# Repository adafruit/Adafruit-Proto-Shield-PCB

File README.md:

## Adafruit Proto Shield for Arduino Unassembled Kit - Stackable - Version R3 PCB

<a href="http://www.adafruit.com/products/2077"><br/>
Click here to purchase one from the Adafruit shop</a>

PCB files for the Adafruit Proto Shield for Arduino Unassembled Kit - Stackable - Version R3. Format is EagleCAD schematic and board layout
* https://www.adafruit.com/product/2077

### Description

This prototyping shield is the best out there (well, we think so, at least), and now is even better with **Version R3** - updated for the most compatibility with just about all the Arduinos! It works with UNO, Mega, Leonardo, NG, Diecimila, Duemilanove, and compatible Arduinos. Yun's and Arduino Ethernets have a chunky Ethernet jack that gets in the way of stacking, you can use the stacking headers included and it will work, just doesn't sit nice and flat.

Check out these awesome specifications:

 * It has a nice standard 0.1"x0.1" prototying grid with big pads
 * Comes with Stacking headers and plain header, choose whichever you want when soldering together
 * A IC pattern for adding DIP ICs up to 20 pins
 * Power rails down the middle and sides
 * A reset button and an extra general use button
 * 2 3mm general use LEDs, red and green, as well as 2 matching resistors
 * A pass-thru ICSP stacking header so you can stack any kind of shield on top, and/or use an AVR programmer
 * A surface-mount chip area for up to 14 SOIC size parts
 * Compatible with tiny breadboards
 * Every pin is brought out!
 * Gold plated pads
 * 2 x 0.1uF capacitors on either side for extra power stability
**Comes as a kit of parts** so you can choose how you want to configure your shield. However its very easy to assemble even for beginning solderers. [More information & instructions are available here](http://learn.adafruit.com/adafruit-proto-shield-arduino).

**Arduino and breadboards are not included!**

### License

Adafruit invests time and resources providing this open source design, please support Adafruit and open-source hardware by purchasing products from [Adafruit](https://www.adafruit.com)!

Designed by Limor Fried/Ladyada for Adafruit Industries.

Creative Commons Attribution/Share-Alike, all text above must be included in any redistribution. See license.txt for additional details.

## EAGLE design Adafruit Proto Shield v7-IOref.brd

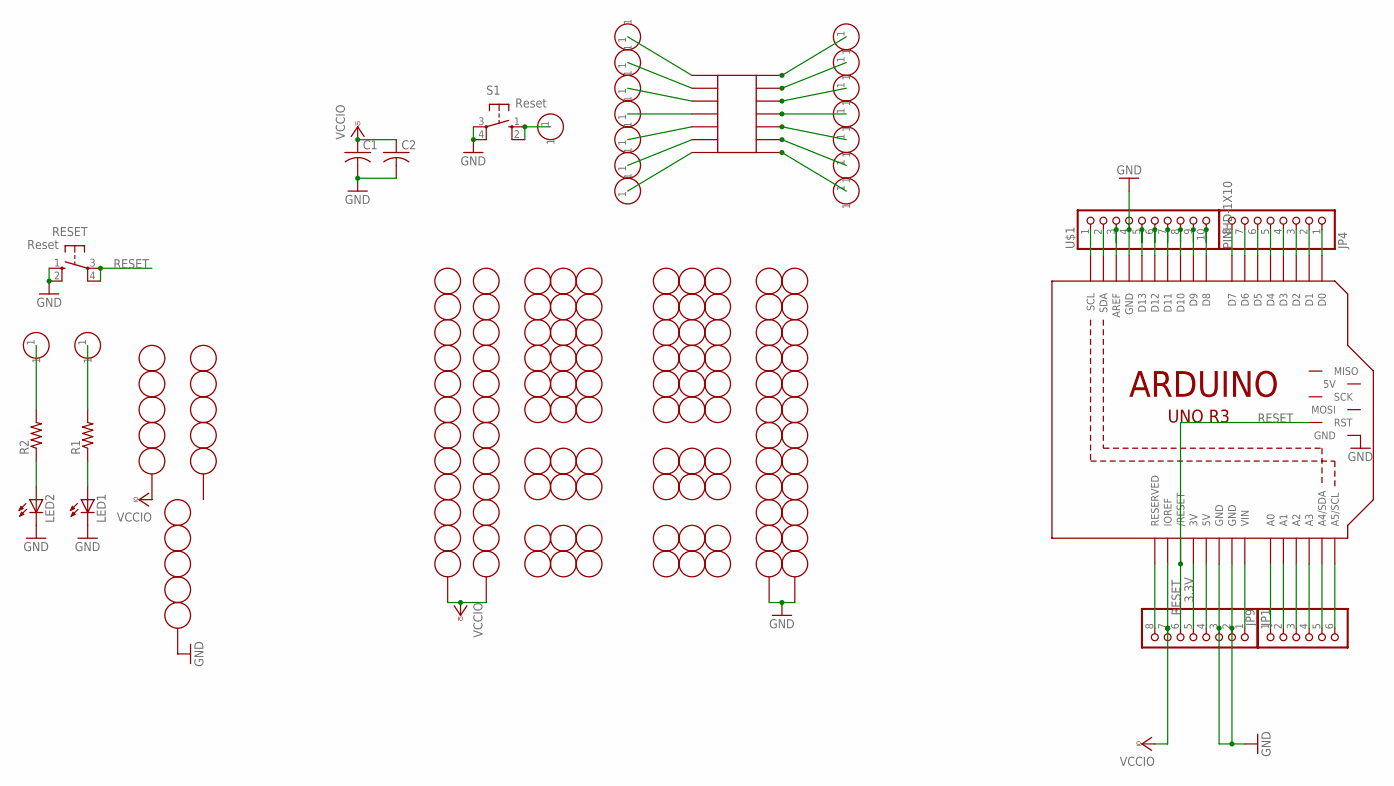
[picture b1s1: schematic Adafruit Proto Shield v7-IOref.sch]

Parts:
C1, C2: C-US025-025X050; C025-025X050
GNDSTRIP1, GNDSTRIP2: 12-STRIP
IC1: SMD-14; SO-14NMW
JP1, JP4: PINHD-1X8BIG; 1X08-BIG
JP9: PINHD-1X6B; 1X06-BIG
LED1, LED2: LED3MM
M1: ARDUINO_R3_ICSP; ARDUINOR3_ICSP
R1, R2: R-US_0207/5V; 0207/5V
RESET: Reset; B3F-10XX
S1: Reset; B3F-10XX
U$1: PINHD-1X10; 1X10-BIG
U$2, U$4, U$6, U$7, U$8, U$9, U$16, U$19, U$25, U$27, U$34, U$35, U$37, U$38, U$39, U$40, U$41: PERFHOLE
U$3, U$24, U$43: 5-STRIP
U$5, U$10, U$11, U$12, U$13, U$14, U$15, U$17, U$18, U$20, U$21, U$22, U$23, U$26, U$28, U$29, U$30, U$31, U$32, U$33: 3-STRIP
VCCSTRIP1, VCCSTRIP2: 12-STRIP

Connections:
3.3V: JP1.5, M1.3V
+5V: JP1.4, M1.5V
GND: C1.2, C2.2, GNDSTRIP1.P$1, GNDSTRIP2.P$1, JP1.2, JP1.3, LED1.K (C), LED2.K (C), M1.GND, M1.GND@1 (GND), M1.GND@2 (GND), M1.GND@3 (GND), RESET.1 (S), RESET.2 (S1), S1.3, S1.4 (P1), U$1.4, U$43.P$3
unnamed: M1.AREF, U$1.3
unnamed: JP1.8, M1.RESERVED
unnamed: M1.D13, U$1.5
unnamed: LED1.A, R1.1
unnamed: R1.2, U$7.1
unnamed: R2.2, U$4.1
unnamed: LED2.A, R2.1
unnamed: M1.D12, U$1.6
unnamed: M1.D11, U$1.7
unnamed: M1.D10, U$1.8
unnamed: M1.D9, U$1.9
unnamed: M1.D8, U$1.10
unnamed: JP9.1, M1.A0
unnamed: JP9.2, M1.A1
unnamed: JP9.3, M1.A2
unnamed: JP9.4, M1.A3
unnamed: JP9.5, M1.A4 (A4/SDA)
unnamed: JP9.6, M1.A5 (A5/SCL)
unnamed: JP4.1, M1.D0
unnamed: JP4.2, M1.D1
unnamed: JP4.3, M1.D2
unnamed: JP4.4, M1.D3
unnamed: JP4.5, M1.D4
unnamed: IC1.P$1, U$2.1
unnamed: IC1.P$2, U$6.1
unnamed: JP4.6, M1.D5
unnamed: JP4.7, M1.D6
unnamed: IC1.P$3, U$8.1
unnamed: IC1.P$4, U$9.1
unnamed: IC1.P$5, U$19.1
unnamed: JP4.8, M1.D7
unnamed: JP1.1, M1.VIN
unnamed: M1.SCL, U$1.1
unnamed: IC1.P$6, U$25.1
unnamed: IC1.P$7, U$27.1
unnamed: IC1.P$8, U$34.1
unnamed: IC1.P$9, U$35.1
unnamed: IC1.P$10, U$37.1
unnamed: M1.SDA, U$1.2
unnamed: IC1.P$11, U$38.1
unnamed: IC1.P$12, U$39.1
unnamed: IC1.P$13, U$40.1
unnamed: IC1.P$14, U$41.1
unnamed: S1.1 (S), S1.2 (S1), U$16.1
RESET: JP1.6, M1.RESET (/RESET), M1.RESET_ICSP (RST), RESET.3, RESET.4 (P1)
VCCIO: C1.1, C2.1, JP1.7, M1.IOREF, U$24.P$3, VCCSTRIP1.P$1, VCCSTRIP2.P$1

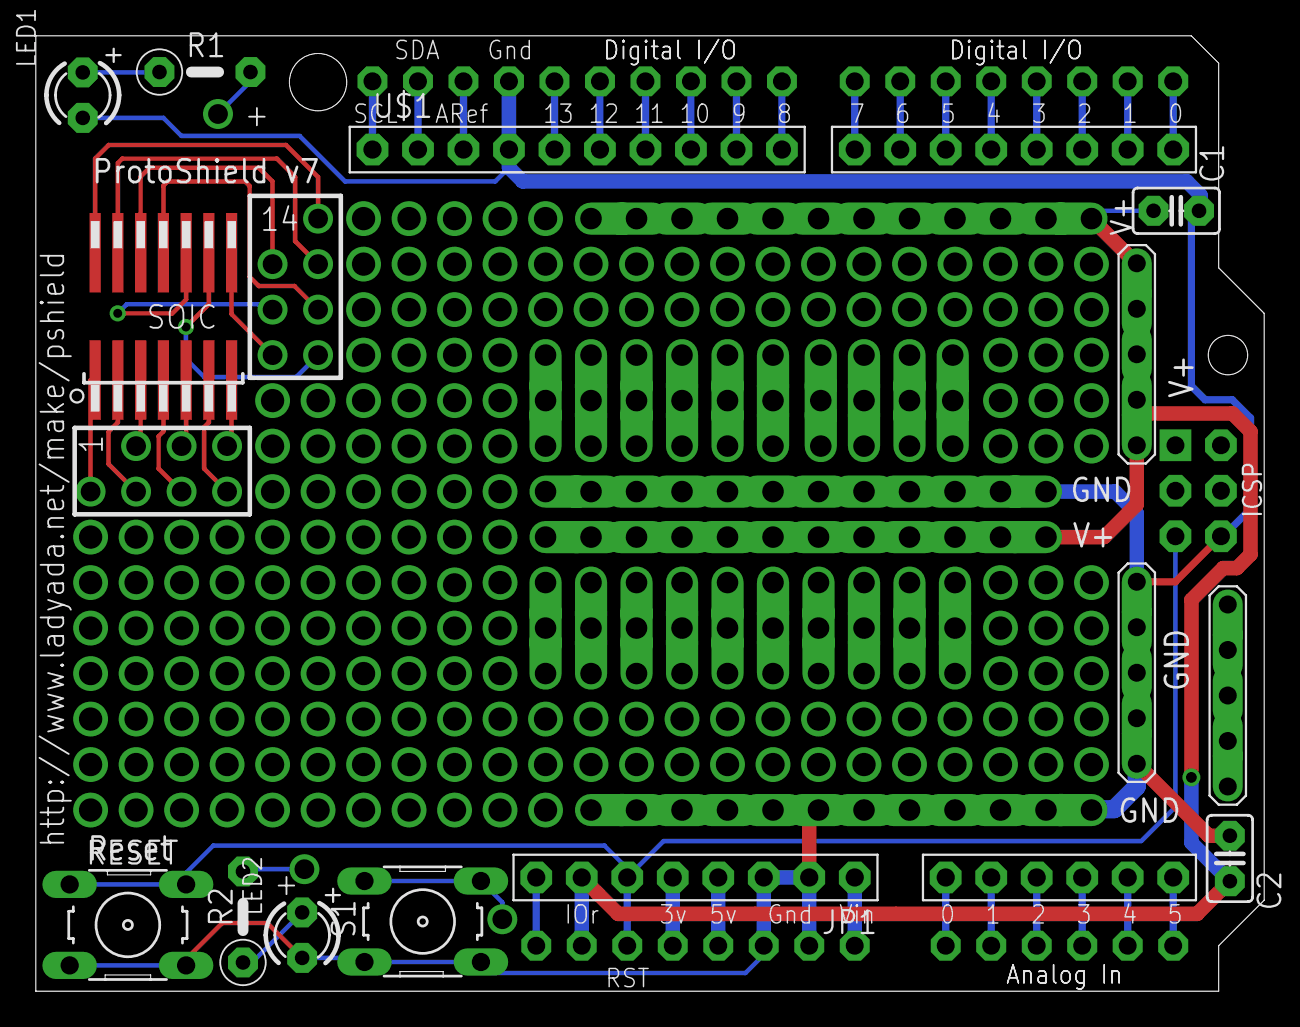
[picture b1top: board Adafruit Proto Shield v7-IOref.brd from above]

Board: 2 copper layers, 68.6 x 53.3 mm, 59 parts (1 on the bottom side), 49 nets.

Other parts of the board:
U$36: ADAFRUIT_9MM

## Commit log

2015-02-20 init
2018-09-15 <EDU>Fix issues with power line width
    In some places, GND and +5V are set to 0.016 while in other places it's 0.032.
    Set to 0.032 everywhere.
    WARNING: I used my free EDU license, the file is for demonstration purpose only!
2018-09-15 Changed +5V to IOref
    In order to be more compatible with new controllers, I changed the connection from +5V to IOref.
2018-09-15 Add .gitignore file
2018-09-15 Add pic, fix ERC, add .lck to .gitignore
2018-09-15 Pic to 300DPI
2019-07-16 updated to use new cookiecutter for pcb repos

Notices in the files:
parts and their libraries:
microbuilder: This work is placed in the public domain, and may be freely used for commercial and non-commercial work with the following conditions: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
